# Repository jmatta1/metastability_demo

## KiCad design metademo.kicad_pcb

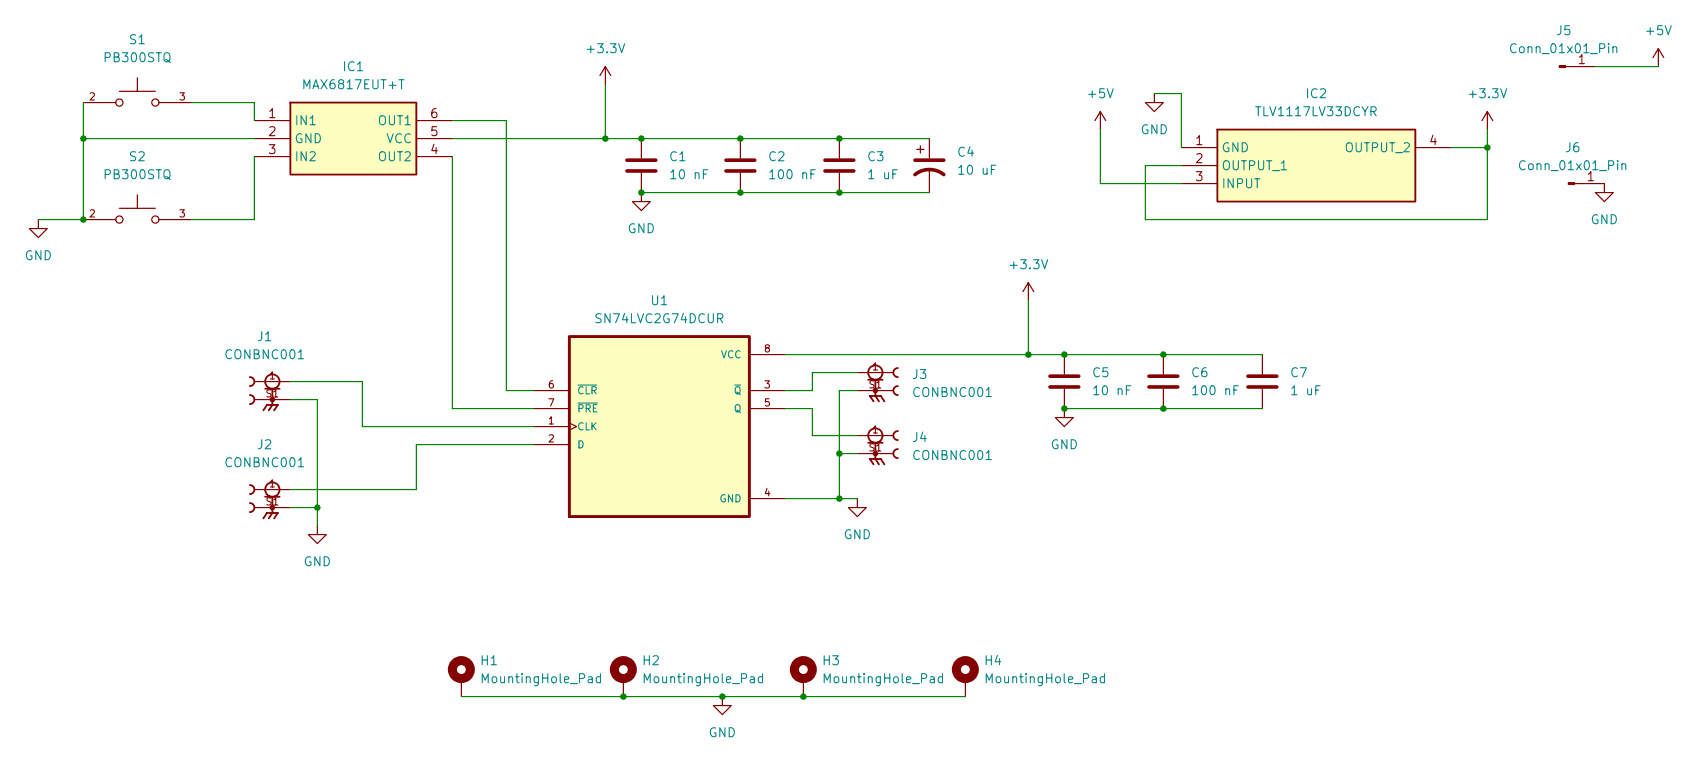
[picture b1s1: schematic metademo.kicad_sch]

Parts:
C1, C5: 10 nF; C_0805_2012Metric_Pad1.18x1.45mm_HandSolder
C2, C6: 100 nF; C_0805_2012Metric_Pad1.18x1.45mm_HandSolder
C3, C7: 1 uF; C_0805_2012Metric_Pad1.18x1.45mm_HandSolder
C4: 10 uF; CAPPRD250W62D630H950
H1, H2, H3, H4: MountingHole_Pad; MountingHole_3.048mm_Pad
IC1: MAX6817EUT+T; SOT95P280X145-6N; Mouser Part Number 700-MAX6817EUTT
IC2: TLV1117LV33DCYR; VREG_TLV1117LV33DCYR; Mouser Part Number 595-TLV1117LV33DCYR
J1, J2, J3, J4: CONBNC001; LINX_CONBNC001
J5, J6: Conn_01x01_Pin; SolderWire-2.5sqmm_1x01_D2.4mm_OD4.4mm
S1, S2: PB300STQ; SW_PB300STQ; PARTREV B
U1: SN74LVC2G74DCUR; SOP50P310X90-8N

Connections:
+3.3V: C1.1, C2.1, C3.1, C4.1, C5.1, C6.1, C7.1, IC1.5 (VCC), IC2.2 (OUTPUT_1), IC2.4 (OUTPUT_2), U1.8 (VCC)
+5V: IC2.3 (INPUT), J5.1
GND: C1.2, C2.2, C3.2, C4.2, C5.2, C6.2, C7.2, H1.1, H2.1, H3.1, H4.1, IC1.2 (GND), IC2.1 (GND), J1.S1, J1.S2, J1.S3, J1.S4, J2.S1, J2.S2, J2.S3, J2.S4, J3.S1, J3.S2, J3.S3, J3.S4, J4.S1, J4.S2, J4.S3, J4.S4, J6.1, S1.2, S2.2, U1.4 (GND)
unnamed: IC1.1 (IN1), S1.3
unnamed: IC1.3 (IN2), S2.3
unnamed: IC1.6 (OUT1), U1.6 (~CLR)
unnamed: IC1.4 (OUT2), U1.7 (~PRE)
unnamed: J1.1, U1.1 (CLK)
unnamed: J2.1, U1.2 (D)
unnamed: J4.1, U1.5 (Q)
unnamed: J3.1, U1.3 (~Q)

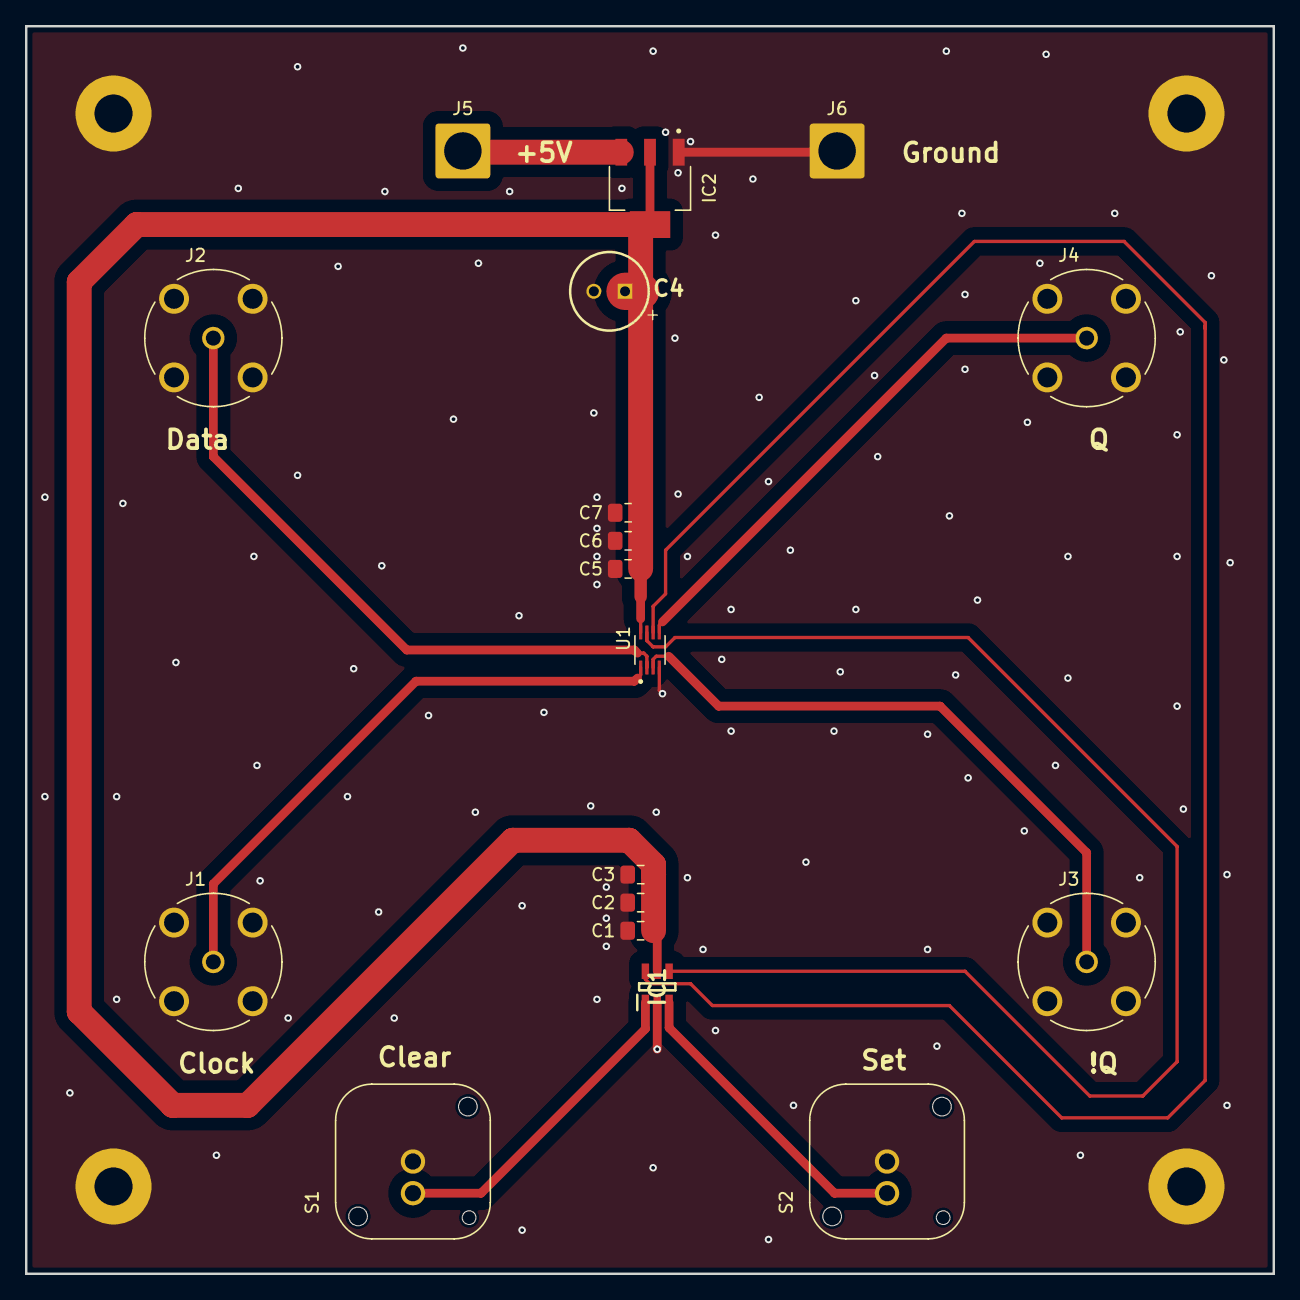
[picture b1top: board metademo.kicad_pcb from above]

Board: 2 copper layers, 100.0 x 100.0 mm, 22 parts (0 on the bottom side), 11 nets.

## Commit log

2026-04-10 initial commit, version 1
